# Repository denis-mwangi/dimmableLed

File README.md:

# dimmableLed

This is a project of dimmable LED using a potentiometer. It has also being implemented in KiCad.

This is a beginner friendly program for testing knowledge in arduino. I've implemented it into a PCB using KiCad 10.

The files containg Arduino code are provided feel free to modify anything.

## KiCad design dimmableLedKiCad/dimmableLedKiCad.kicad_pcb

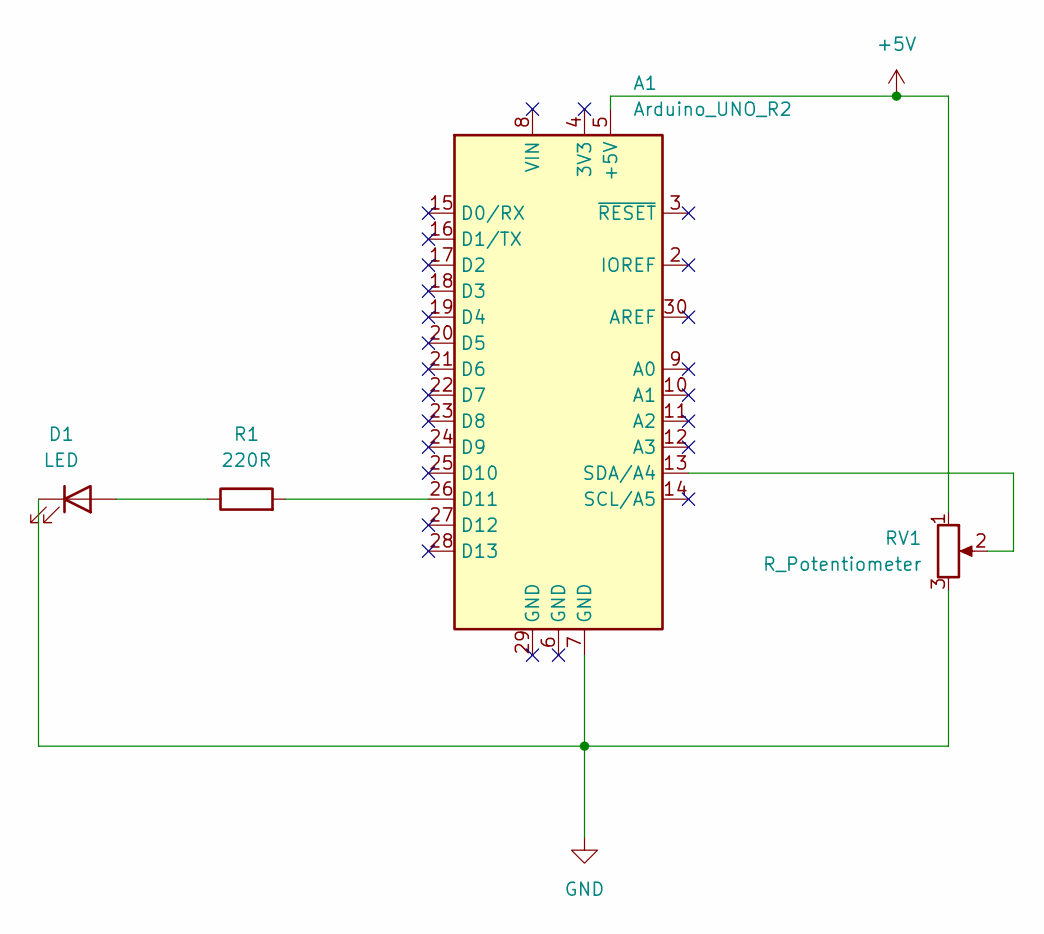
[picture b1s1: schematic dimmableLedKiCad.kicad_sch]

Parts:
A1: Arduino_UNO_R2
D1: LED; LED_D5.0mm_Clear
R1: 220R; R_Axial_DIN0411_L9.9mm_D3.6mm_P15.24mm_Horizontal
RV1: R_Potentiometer; Potentiometer_ACP_CA14V-15_Vertical_Hole

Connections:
+5V: A1.5 (+5V), RV1.1
GND: A1.7 (GND), D1.1 (K), RV1.3
unnamed: A1.26 (D11), R1.2
unnamed: A1.13 (SDA/A4), RV1.2
unnamed: D1.2 (A), R1.1

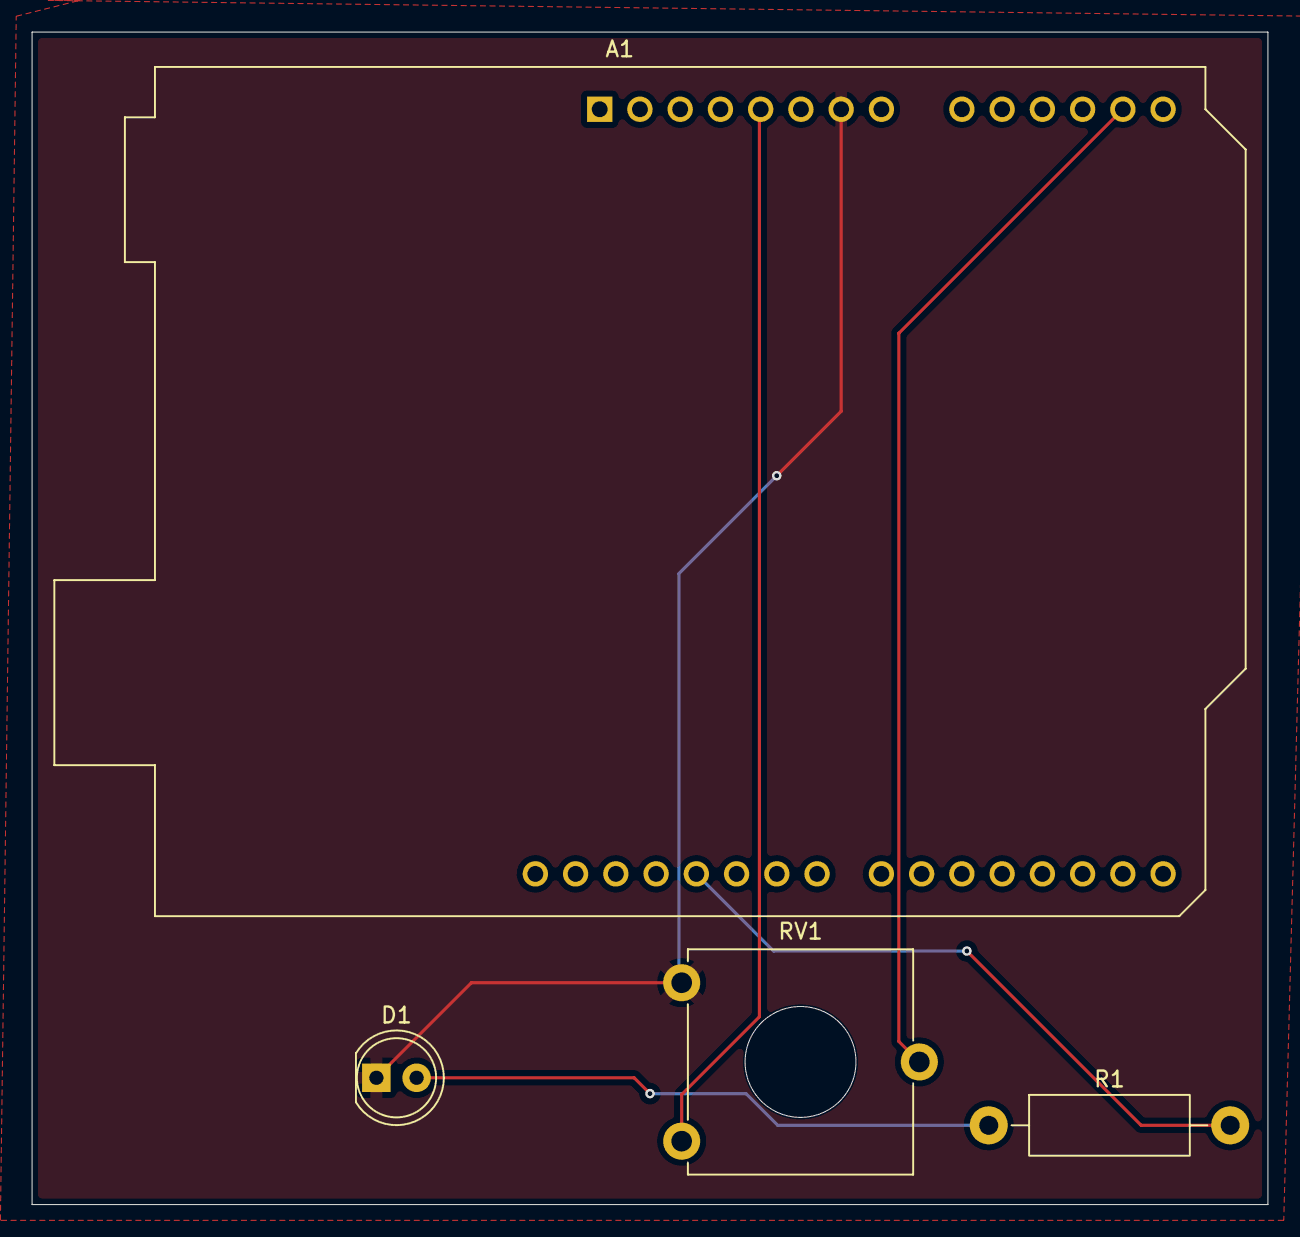
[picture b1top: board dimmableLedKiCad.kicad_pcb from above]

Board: 2 copper layers, 78.0 x 74.0 mm, 4 parts (0 on the bottom side), 5 nets.
